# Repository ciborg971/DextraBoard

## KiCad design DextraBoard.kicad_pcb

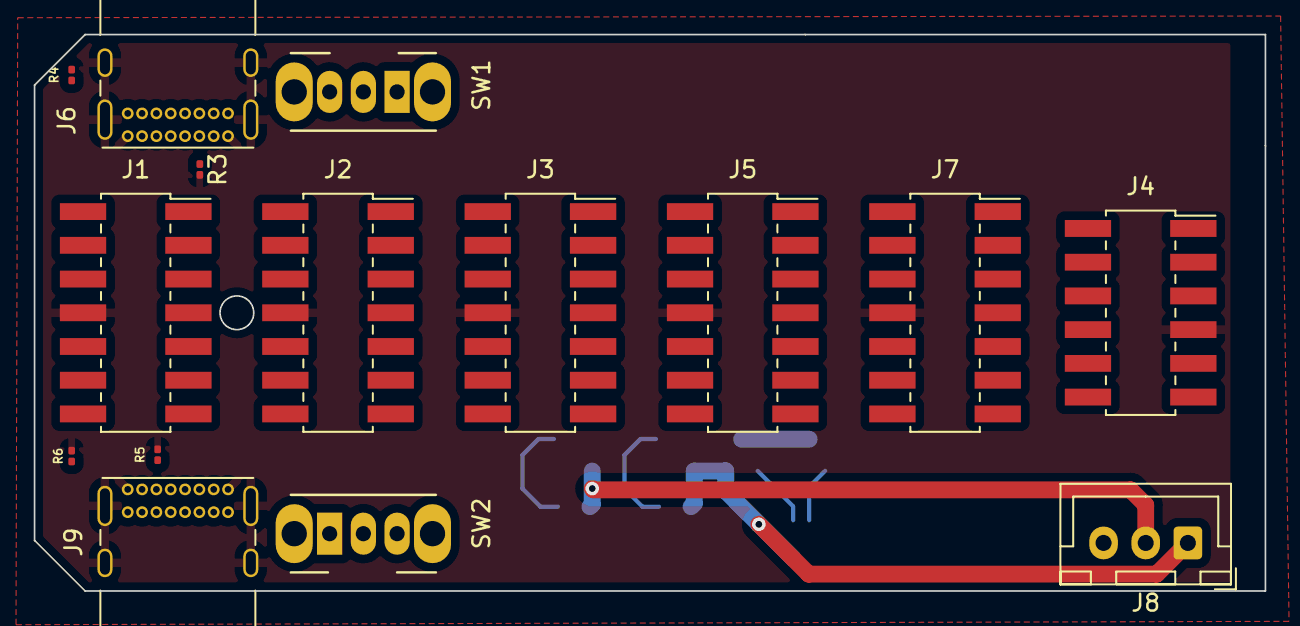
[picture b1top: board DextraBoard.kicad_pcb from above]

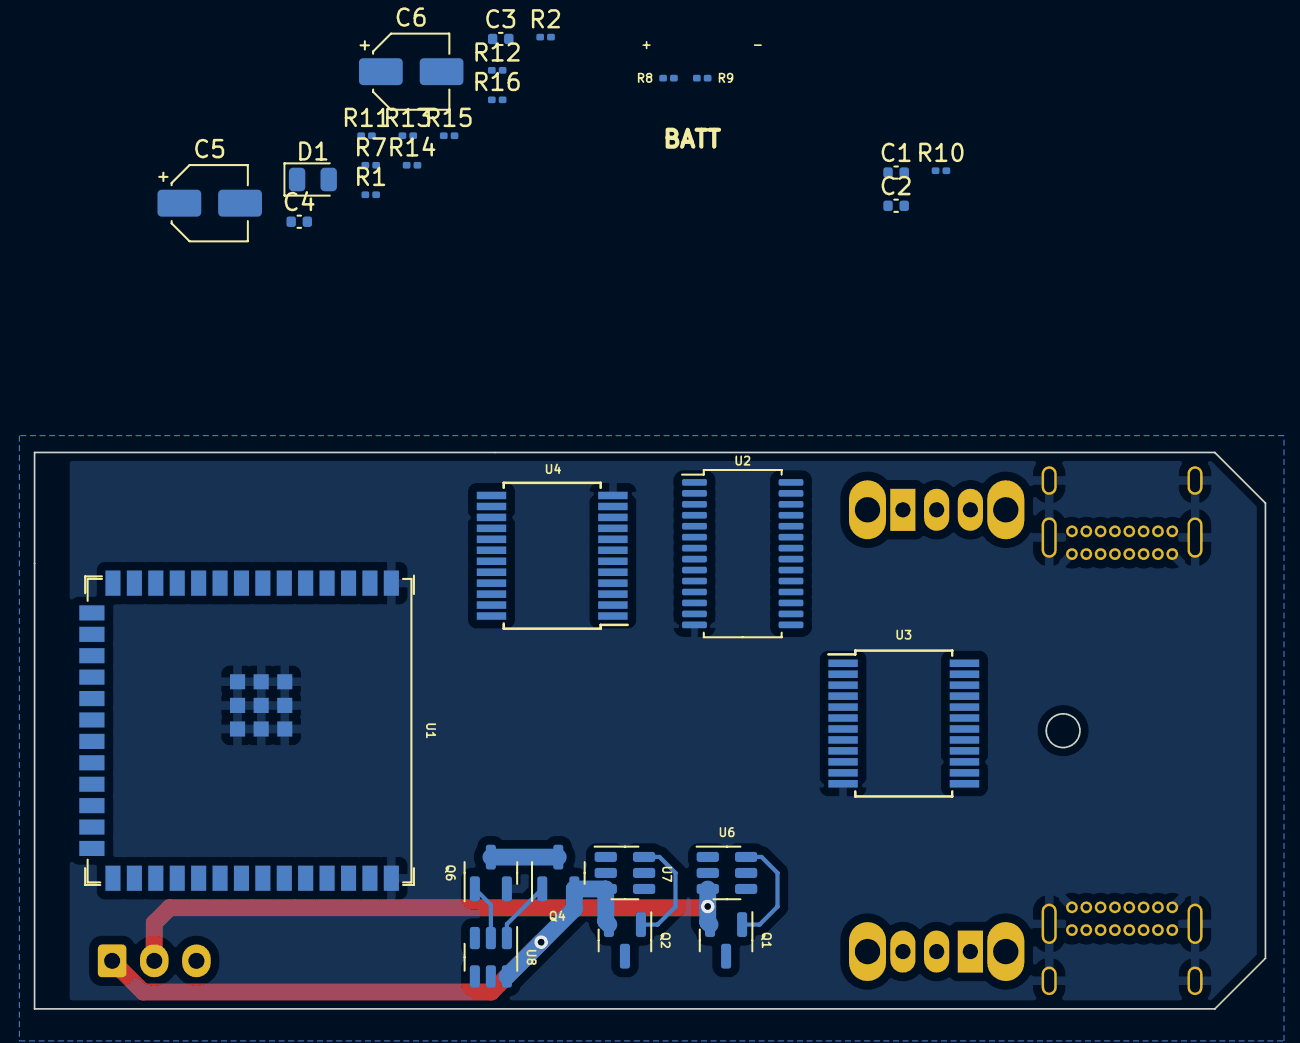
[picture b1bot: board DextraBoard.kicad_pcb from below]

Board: 4 copper layers, 73.0 x 33.0 mm, 45 parts (30 on the bottom side), 88 nets.

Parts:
C1, C2, C3, C4: 0.1uF; C_0402_1005Metric
C5, C6: 0.1uF; CP_Elec_4x3
D1: LED; LED_0805_2012Metric
J1, J2, J3, J5, J7: Conn_02x07_Counter_Clockwise; PinSocket_2x07_P2.00mm_Vertical_SMD
J4: Conn_02x06_Counter_Clockwise; PinSocket_2x06_P2.00mm_Vertical_SMD
J6, J9: USB_C_Receptacle_USB2.0; USB_C_Receptacle_GCT_USB4085
J8: Conn_01x03_Female; JST_XH_B3B-XH-A_1x03_P2.50mm_Vertical
Q1, Q2, Q4, Q6: HX2300A; SOT-23
R1, R2: 100R; R_0201_0603Metric
R3, R4, R5, R6: 5K1; R_0201_0603Metric
R7, R13: R; R_0201_0603Metric
R8: 2M; R_0201_0603Metric
R9: 1M; R_0201_0603Metric
R10: 10K; R_0201_0603Metric
R11, R12: 1K; R_0201_0603Metric
R14: 2K; R_0201_0603Metric
R15, R16: 330R; R_0201_0603Metric
SW1, SW2: SW_SPDT; SW_CuK_OS102011MA1QN1_SPDT_Angled
U1: ESP32-S3-WROOM-1; ESP32-S3-WROOM-1U
U2: PCA9685PW; TSSOP-28_4.4x9.7mm_P0.65mm
U3, U4: CD74HC4067SM; SSOP-24_5.3x8.2mm_P0.65mm
U6, U7: HY2213; SOT-23-6
U8: HY2120; SOT-23-6

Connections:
+3.3V: R13.2, U2.28 (VDD), U3.24 (VCC), U4.24 (VCC)
+3V3: J1.7, J2.7, J3.7, J4.4, J5.7, J7.7, R10.1, U1.2 (3V3)
+5V: J1.1, J2.1, J3.1, J4.1, J5.1, J7.1
+BATT: C3.1, J8.3, R1.1, R8.2, R9.2, R11.1, R15.2, SW1.3 (C), SW2.3 (C)
-BATT: C4.2, C5.2, C6.2, J8.1, Q2.2 (S), Q4.2 (S), U7.3 (VSS), U8.6 (VSS)
/ANA0: J4.10, U1.39 (GPIO1/TOUCH1/ADC1_CH0)
/ANA1: J4.9, U1.38 (GPIO2/TOUCH2/ADC1_CH1)
/ANA2: J4.8, U1.15 (GPIO3/TOUCH3/ADC1_CH2)
/ANA3: U1.4 (GPIO4/TOUCH4/ADC1_CH3), U3.1 (COM)
/ANA4: U1.5 (GPIO5/TOUCH5/ADC1_CH4), U4.1 (COM)
/HY_VDD: C5.1, R16.1, U8.5 (VDD)
/IO7: U1.7 (GPIO7/TOUCH7/ADC1_CH6), U3.10 (S0), U4.10 (S0)
/IO8: U1.12 (GPIO8/TOUCH8/ADC1_CH7/SUBSPICS1), U3.11 (S1), U4.11 (S1)
/IO9: U1.17 (GPIO9/TOUCH9/ADC1_CH8/FSPIHD/SUBSPIHD), U3.14 (S2), U4.14 (S2)
/IO10: U1.18 (GPIO10/TOUCH10/ADC1_CH9/FSPICS0/FSPIIO4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), U3.13 (S3), U4.13 (S3)
/IO13: J4.12, U1.21 (GPIO13/TOUCH13/ADC2_CH2/FSPIQ/FSPIIO7/S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)
/IO14: J4.6, U1.22 (GPIO14/TOUCH14/ADC2_CH3/FSPIWP/FSPIDQS/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)
/IO15: J4.11, U1.8 (GPIO15/U0RTS/ADC2_CH4/XTAL_32K_P)
/MID_BAT: C3.2, C4.1, J8.2, Q1.2 (S), R2.1, R12.1, R16.2, U6.3 (VSS)
/N76E003s (PWM + ADC + IO)/MUX_CH0: J1.14, U3.9 (I0)
/N76E003s (PWM + ADC + IO)/MUX_CH1: J1.13, U3.8 (I1)
/N76E003s (PWM + ADC + IO)/MUX_CH2: J1.12, U3.7 (I2)
/N76E003s (PWM + ADC + IO)/MUX_CH3: J1.11, U3.6 (I3)
/N76E003s (PWM + ADC + IO)/MUX_CH4: J1.10, U3.5 (I4)
/N76E003s (PWM + ADC + IO)/MUX_CH5: J1.9, U3.4 (I5)
/N76E003s (PWM + ADC + IO)/MUX_CH6: J2.14, U3.3 (I6)
/N76E003s (PWM + ADC + IO)/MUX_CH7: J2.13, U3.2 (I7)
/N76E003s (PWM + ADC + IO)/MUX_CH8: J2.12, U3.23 (I8)
/N76E003s (PWM + ADC + IO)/MUX_CH9: J2.11, U3.22 (I9)
/N76E003s (PWM + ADC + IO)/MUX_CH10: J2.10, U3.21 (I10)
/N76E003s (PWM + ADC + IO)/MUX_CH11: J2.9, U3.20 (I11)
/N76E003s (PWM + ADC + IO)/MUX_CH12: J3.14, U3.19 (I12)
/N76E003s (PWM + ADC + IO)/MUX_CH13: J3.13, U3.18 (I13)
/N76E003s (PWM + ADC + IO)/MUX_CH14: J3.12, U3.17 (I14)
/N76E003s (PWM + ADC + IO)/MUX_CH15: J3.11, U3.16 (I15)
/N76E003s (PWM + ADC + IO)/MUX_CH16: J3.10, U4.9 (I0)
/N76E003s (PWM + ADC + IO)/MUX_CH17: J3.9, U4.8 (I1)
/N76E003s (PWM + ADC + IO)/MUX_CH18: J5.14, U4.7 (I2)
/N76E003s (PWM + ADC + IO)/MUX_CH19: J5.13, U4.6 (I3)
/N76E003s (PWM + ADC + IO)/MUX_CH20: J5.12, U4.5 (I4)
/N76E003s (PWM + ADC + IO)/MUX_CH21: J5.11, U4.4 (I5)
/N76E003s (PWM + ADC + IO)/MUX_CH22: J5.10, U4.3 (I6)
/N76E003s (PWM + ADC + IO)/MUX_CH23: J5.9, U4.2 (I7)
/N76E003s (PWM + ADC + IO)/MUX_CH24: J7.14, U4.23 (I8)
/N76E003s (PWM + ADC + IO)/MUX_CH25: J7.13, U4.22 (I9)
/N76E003s (PWM + ADC + IO)/MUX_CH26: J7.12, U4.21 (I10)
/N76E003s (PWM + ADC + IO)/MUX_CH27: J7.11, U4.20 (I11)
/N76E003s (PWM + ADC + IO)/MUX_CH28: J7.10, U4.19 (I12)
/N76E003s (PWM + ADC + IO)/MUX_CH29: J7.9, U4.18 (I13)
/N76E003s (PWM + ADC + IO)/PWM4: J1.4, J5.4, U2.10 (LED4)
/N76E003s (PWM + ADC + IO)/PWM5: J1.5, J5.5, U2.11 (LED5)
/N76E003s (PWM + ADC + IO)/PWM6: J3.2, U2.12 (LED6)
/N76E003s (PWM + ADC + IO)/PWM7: J3.3, U2.13 (LED7)
/N76E003s (PWM + ADC + IO)/PWM8: J3.4, U2.15 (LED8)
/N76E003s (PWM + ADC + IO)/PWM9: J3.5, U2.16 (LED9)
/N76E003s (PWM + ADC + IO)/PWM10: J2.2, U2.17 (LED10)
/N76E003s (PWM + ADC + IO)/PWM11: J2.3, U2.18 (LED11)
/N76E003s (PWM + ADC + IO)/PWM12: J2.4, U2.19 (LED12)
/N76E003s (PWM + ADC + IO)/PWM13: J2.5, U2.20 (LED13)
/N76E003s (PWM + ADC + IO)/PWM14: J1.2, U2.21 (LED14)
/N76E003s (PWM + ADC + IO)/PWM15: J1.3, U2.22 (LED15)
/OC: Q6.1 (G), U8.2 (OC)
/OD: Q4.1 (G), U8.1 (OD)
/PWM0: J4.2, J7.2, U1.23 (GPIO21), U2.6 (LED0)
/PWM1: J4.3, J7.3, U1.26 (GPIO45), U2.7 (LED1)
/PWM2: J5.2, J7.5, U1.16 (GPIO46), U2.8 (LED2)
/PWM3: J5.3, J7.4, U1.25 (GPIO48/SPICLK_N/SUBSPICLK_N_DIFF), U2.9 (LED3)
/USB_DN: J6.A7 (D-), J6.B7 (D-), J9.A7 (D-), J9.B7 (D-), U1.13 (GPIO19/U1RTS/ADC2_CH8/CLK_OUT2/USB_D-)
/USB_DP: J6.A6 (D+), J6.B6 (D+), J9.A6 (D+), J9.B6 (D+), U1.14 (GPIO20/U1CTS/ADC2_CH9/CLK_OUT1/USB_D+)
/VIN: SW1.2 (B), SW2.2 (B)
/VSENSE: R8.1, U1.6 (GPIO6/TOUCH6/ADC1_CH5)
GND: C1.1, C2.1, J1.8, J2.8, J3.8, J4.7, J5.8, J6.A1 (GND), J6.A12 (GND), J6.B1 (GND), J6.B12 (GND), J6.S1 (SHIELD), J7.8, J9.A1 (GND), J9.A12 (GND), J9.B1 (GND), J9.B12 (GND), J9.S1 (SHIELD), Q6.2 (S), R3.2, R4.2, R5.2, R6.2, R7.2, R9.1, R14.1, U1.1 (GND), U1.40 (GND), U1.41 (GND), U2.14 (VSS), U3.12 (GND), U3.15 (~E), U4.12 (GND), U4.15 (~E)
unnamed: C1.2, C2.2, R10.2
unnamed: C6.1, R15.1, U8.4 (VC)
unnamed: D1.2 (A), R13.1
unnamed: J6.A5 (CC1), R3.1
unnamed: J6.B5 (CC2), R4.1
unnamed: J9.A5 (CC1), R5.1
unnamed: J9.B5 (CC2), R6.1
unnamed: Q1.1 (G), U6.6 (OUT)
unnamed: Q1.3 (D), R11.2
unnamed: Q2.1 (G), U7.6 (OUT)
unnamed: Q2.3 (D), R12.2
unnamed: Q4.3 (D), Q6.3 (D)
unnamed: R1.2, U6.2 (VDD)
unnamed: R2.2, U7.2 (VDD)
unnamed: R14.2, U8.3 (CS)
VBUS: J6.A4 (VBUS), J6.A9 (VBUS), J6.B4 (VBUS), J6.B9 (VBUS), J9.A4 (VBUS), J9.A9 (VBUS), J9.B4 (VBUS), J9.B9 (VBUS), SW1.1 (A), SW2.1 (A)

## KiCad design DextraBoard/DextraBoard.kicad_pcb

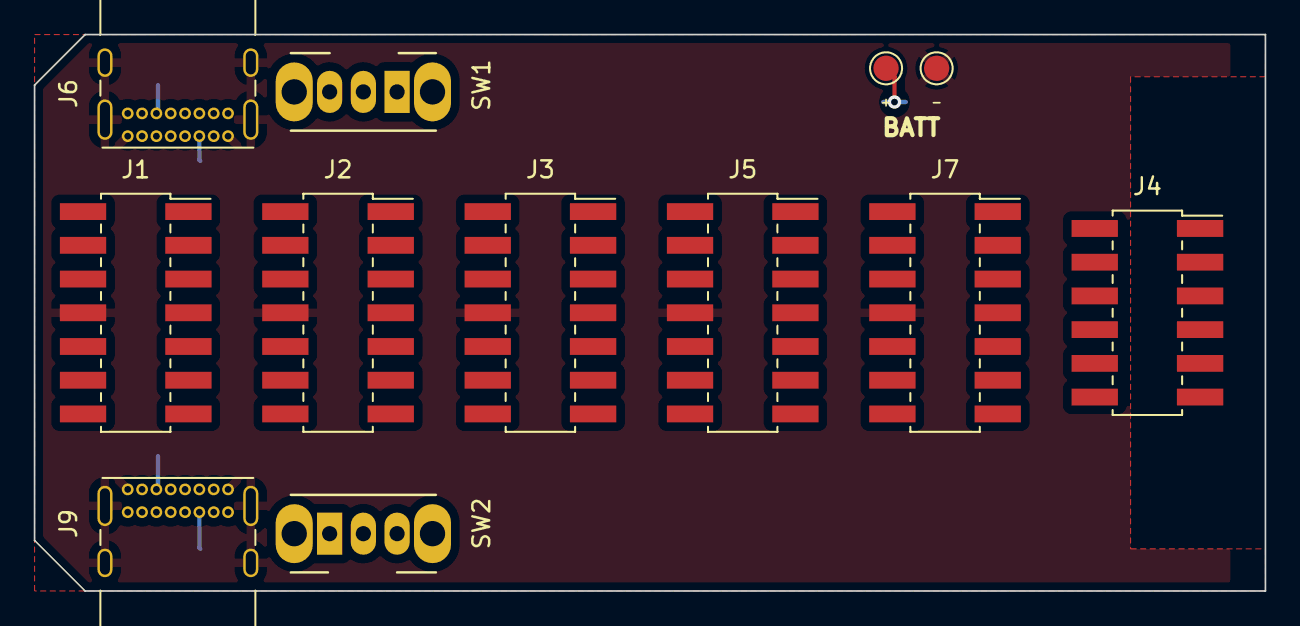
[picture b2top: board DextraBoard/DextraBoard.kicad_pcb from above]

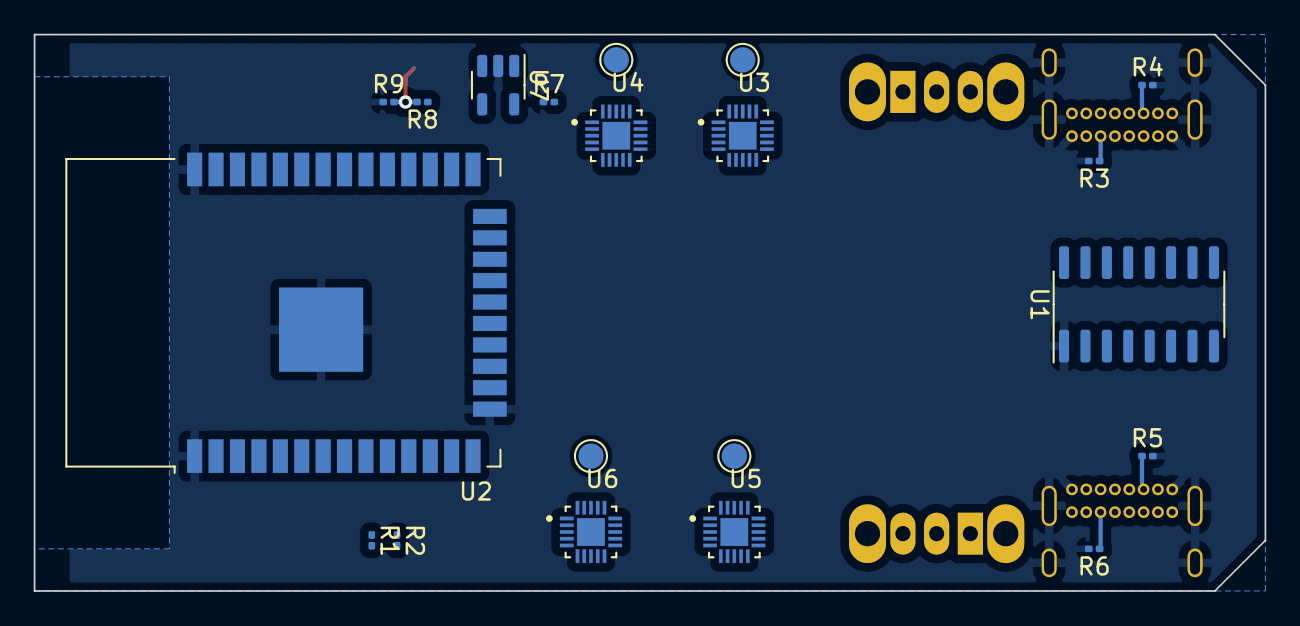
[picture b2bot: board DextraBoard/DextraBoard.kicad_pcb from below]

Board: 2 copper layers, 73.0 x 33.0 mm, 32 parts (20 on the bottom side), 83 nets.

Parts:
J1, J2, J3, J5, J7: Conn_02x07_Counter_Clockwise; PinSocket_2x07_P2.00mm_Vertical_SMD
J4: Conn_02x06_Counter_Clockwise; PinSocket_2x06_P2.00mm_Vertical_SMD
J6, J9: USB_C_Receptacle_USB2.0; USB_C_Receptacle_GCT_USB4085
R1, R2: 10K; R_0201_0603Metric
R3, R4, R5, R6: 5K1; R_0201_0603Metric
R7: R; R_0201_0603Metric
R8, R9: 1M; R_0201_0603Metric
SW1, SW2: SW_SPDT; SW_CuK_OS102011MA1QN1_SPDT_Angled
TP1, TP2, TP3, TP4, TP5, TP6: TestPoint; TestPoint_Pad_D1.5mm
U1: CH340C; SOIC-16_3.9x9.9mm_P1.27mm
U2: ESP32-WROOM-32D; ESP32-WROOM-32
U3, U4, U5, U6: N76E003AQ20; QFN40P300X300X80-21N
U7: MCP73811T-420I-OT; SOT-23-5

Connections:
+3V3: J1.7, J2.7, J3.7, J4.4, J5.7, J7.7, R1.1, R2.1, U2.2 (VDD), U3.5 (VDD), U4.5 (VDD), U5.5 (VDD), U6.5 (VDD)
+5V: J1.1, J2.1, J3.1, J4.1, J5.1, J7.1
+BATT: R8.2, R9.2, SW1.3 (C), SW2.3 (C), TP1.1, U7.3 (VBAT)
/ANA0: J7.10, U2.9 (IO33)
/ANA1: J7.9, U2.6 (IO34)
/ANA2: J4.10, U2.7 (IO35)
/ANA3: J4.9, U2.5 (SENSOR_VN)
/ANA4: J4.8, U2.4 (SENSOR_VP)
/I2C_SCL: R2.2, U2.36 (IO22), U3.11 (P1.3/SCL), U4.11 (P1.3/SCL), U5.11 (P1.3/SCL), U6.11 (P1.3/SCL)
/I2C_SDA: R1.2, U2.33 (IO21), U3.10 (P1.4/SDA/FB/PWM1), U4.10 (P1.4/SDA/FB/PWM1), U5.10 (P1.4/SDA/FB/PWM1), U6.10 (P1.4/SDA/FB/PWM1)
/N76E003s (PWM + ADC + IO)/ANA0_0: J1.14, U3.2 (P1.7/~INT1/AIN0)
/N76E003s (PWM + ADC + IO)/ANA0_1: J1.13, U3.17 (P3.0/~INT0/OSCIN/AIN1)
/N76E003s (PWM + ADC + IO)/ANA0_2: J1.12, U3.1 (P0.7/RXD/AIN2)
/N76E003s (PWM + ADC + IO)/ANA0_3: J1.11, U3.19 (P0.6/TXD/AIN3)
/N76E003s (PWM + ADC + IO)/ANA0_4: J1.10, U3.20 (P0.5/PWM2/IC6/T0/AIN4)
/N76E003s (PWM + ADC + IO)/ANA0_5: J1.9, U3.16 (P0.4/AIN5/STADC/PWM3/IC3)
/N76E003s (PWM + ADC + IO)/ANA0_6: J2.14, U3.15 (P0.3/PWM5/IC5/AIN6)
/N76E003s (PWM + ADC + IO)/ANA1_0: J2.13, U4.2 (P1.7/~INT1/AIN0)
/N76E003s (PWM + ADC + IO)/ANA1_1: J2.12, U4.17 (P3.0/~INT0/OSCIN/AIN1)
/N76E003s (PWM + ADC + IO)/ANA1_2: J2.11, U4.1 (P0.7/RXD/AIN2)
/N76E003s (PWM + ADC + IO)/ANA1_3: J2.10, U4.19 (P0.6/TXD/AIN3)
/N76E003s (PWM + ADC + IO)/ANA1_4: J2.9, U4.20 (P0.5/PWM2/IC6/T0/AIN4)
/N76E003s (PWM + ADC + IO)/ANA1_5: J3.14, U4.16 (P0.4/AIN5/STADC/PWM3/IC3)
/N76E003s (PWM + ADC + IO)/ANA1_6: J3.13, U4.15 (P0.3/PWM5/IC5/AIN6)
/N76E003s (PWM + ADC + IO)/ANA2_0: J3.12, U5.2 (P1.7/~INT1/AIN0)
/N76E003s (PWM + ADC + IO)/ANA2_1: J3.11, U5.17 (P3.0/~INT0/OSCIN/AIN1)
/N76E003s (PWM + ADC + IO)/ANA2_2: J3.10, U5.1 (P0.7/RXD/AIN2)
/N76E003s (PWM + ADC + IO)/ANA2_3: J3.9, U5.19 (P0.6/TXD/AIN3)
/N76E003s (PWM + ADC + IO)/ANA2_4: J5.14, U5.20 (P0.5/PWM2/IC6/T0/AIN4)
/N76E003s (PWM + ADC + IO)/ANA2_5: J5.13, U5.16 (P0.4/AIN5/STADC/PWM3/IC3)
/N76E003s (PWM + ADC + IO)/ANA2_6: J5.12, U5.15 (P0.3/PWM5/IC5/AIN6)
/N76E003s (PWM + ADC + IO)/ANA3_0: J5.11, U6.2 (P1.7/~INT1/AIN0)
/N76E003s (PWM + ADC + IO)/ANA3_1: J5.10, U6.17 (P3.0/~INT0/OSCIN/AIN1)
/N76E003s (PWM + ADC + IO)/ANA3_2: J5.9, U6.1 (P0.7/RXD/AIN2)
/N76E003s (PWM + ADC + IO)/ANA3_3: J7.14, U6.19 (P0.6/TXD/AIN3)
/N76E003s (PWM + ADC + IO)/ANA3_4: J7.13, U6.20 (P0.5/PWM2/IC6/T0/AIN4)
/N76E003s (PWM + ADC + IO)/ANA3_5: J7.12, U6.16 (P0.4/AIN5/STADC/PWM3/IC3)
/N76E003s (PWM + ADC + IO)/ANA3_6: J7.11, U6.15 (P0.3/PWM5/IC5/AIN6)
/N76E003s (PWM + ADC + IO)/PWM0_0: J1.2, U3.9 (P1.2/PWM0/IC0)
/N76E003s (PWM + ADC + IO)/PWM0_1: J1.3, U3.8 (P1.1/PWM1/IC1/AIN7/CLO)
/N76E003s (PWM + ADC + IO)/PWM0_2: J1.4, U3.7 (P1.0/PWM2/IC2/SPCLK)
/N76E003s (PWM + ADC + IO)/PWM0_3: J1.5, U3.12 (P0.0/PWM3/IC3/MOSI/T1)
/N76E003s (PWM + ADC + IO)/PWM0_4: J2.2, U3.13 (P0.1/PWM4/IC4/MISO)
/N76E003s (PWM + ADC + IO)/PWM0_5: J2.3, U3.6 (P1.5/PWM5/IC7/~SS)
/N76E003s (PWM + ADC + IO)/PWM1_0: J2.4, U4.9 (P1.2/PWM0/IC0)
/N76E003s (PWM + ADC + IO)/PWM1_1: J2.5, U4.8 (P1.1/PWM1/IC1/AIN7/CLO)
/N76E003s (PWM + ADC + IO)/PWM1_2: J3.2, U4.7 (P1.0/PWM2/IC2/SPCLK)
/N76E003s (PWM + ADC + IO)/PWM1_3: J3.3, U4.12 (P0.0/PWM3/IC3/MOSI/T1)
/N76E003s (PWM + ADC + IO)/PWM1_4: J3.4, U4.13 (P0.1/PWM4/IC4/MISO)
/N76E003s (PWM + ADC + IO)/PWM1_5: J3.5, U4.6 (P1.5/PWM5/IC7/~SS)
/N76E003s (PWM + ADC + IO)/PWM2_0: J5.2, U5.9 (P1.2/PWM0/IC0)
/N76E003s (PWM + ADC + IO)/PWM2_1: J5.3, U5.8 (P1.1/PWM1/IC1/AIN7/CLO)
/N76E003s (PWM + ADC + IO)/PWM2_2: J5.4, U5.7 (P1.0/PWM2/IC2/SPCLK)
/N76E003s (PWM + ADC + IO)/PWM2_3: J5.5, U5.12 (P0.0/PWM3/IC3/MOSI/T1)
/N76E003s (PWM + ADC + IO)/PWM2_4: J7.2, U5.13 (P0.1/PWM4/IC4/MISO)
/N76E003s (PWM + ADC + IO)/PWM2_5: J7.3, U5.6 (P1.5/PWM5/IC7/~SS)
/N76E003s (PWM + ADC + IO)/PWM3_0: J7.4, U6.9 (P1.2/PWM0/IC0)
/N76E003s (PWM + ADC + IO)/PWM3_1: J7.5, U6.8 (P1.1/PWM1/IC1/AIN7/CLO)
/N76E003s (PWM + ADC + IO)/RXD0: J1.6, U3.14 (P0.2/ICPCK/OCDCK/RXD_1)
/N76E003s (PWM + ADC + IO)/RXD1: J3.6, U4.14 (P0.2/ICPCK/OCDCK/RXD_1)
/N76E003s (PWM + ADC + IO)/RXD2: J7.6, U5.14 (P0.2/ICPCK/OCDCK/RXD_1)
/N76E003s (PWM + ADC + IO)/RXD3: J4.6, U6.14 (P0.2/ICPCK/OCDCK/RXD_1)
/N76E003s (PWM + ADC + IO)/TXD0: J2.6, U3.4 (P1.6/ICPDA/OCDDA/TXD_1)
/N76E003s (PWM + ADC + IO)/TXD1: J5.6, U4.4 (P1.6/ICPDA/OCDDA/TXD_1)
/N76E003s (PWM + ADC + IO)/TXD2: J4.5, U5.4 (P1.6/ICPDA/OCDDA/TXD_1)
/N76E003s (PWM + ADC + IO)/TXD3: J4.11, J4.12, U6.4 (P1.6/ICPDA/OCDDA/TXD_1)
/PWM0: J4.2, U2.11 (IO26)
/PWM1: J4.3, U2.12 (IO27)
/USB_DN: J6.A7 (D-), J6.B7 (D-), J9.A7 (D-), J9.B7 (D-), U1.6 (UD-)
/USB_DP: J6.A6 (D+), J6.B6 (D+), J9.A6 (D+), J9.B6 (D+), U1.5 (UD+)
/VIN: SW1.2 (B), SW2.2 (B)
/VSENSE: R8.1, U2.8 (IO32)
GND: J1.8, J2.8, J3.8, J4.7, J5.8, J6.A1 (GND), J6.A12 (GND), J6.B1 (GND), J6.B12 (GND), J6.S1 (SHIELD), J7.8, J9.A1 (GND), J9.A12 (GND), J9.B1 (GND), J9.B12 (GND), J9.S1 (SHIELD), R3.2, R4.2, R5.2, R6.2, R7.1, R9.1, TP2.1, U1.1 (GND), U2.1 (GND), U2.15 (GND), U2.38 (GND), U2.39 (GND), U3.3 (GND), U3.21 (EXP), U4.3 (GND), U4.21 (EXP), U5.3 (GND), U5.21 (EXP), U6.3 (GND), U6.21 (EXP), U7.2 (VSS)
unnamed: J6.A5 (CC1), R3.1
unnamed: J6.B5 (CC2), R4.1
unnamed: J9.A5 (CC1), R5.1
unnamed: J9.B5 (CC2), R6.1
unnamed: R7.2, U7.5 (PROG)
unnamed: TP3.1, U3.18 (P2.0/~RST)
unnamed: TP4.1, U4.18 (P2.0/~RST)
unnamed: TP5.1, U5.18 (P2.0/~RST)
unnamed: TP6.1, U6.18 (P2.0/~RST)
VBUS: J6.A4 (VBUS), J6.A9 (VBUS), J6.B4 (VBUS), J6.B9 (VBUS), J9.A4 (VBUS), J9.A9 (VBUS), J9.B4 (VBUS), J9.B9 (VBUS), SW1.1 (A), SW2.1 (A), U7.4 (VDD)

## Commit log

2022-08-24 component placement
2022-08-24 replaced esp32wroom by esp32 pico d4 and moved all component on one side
2022-12-01 redesigned everything x)
    new BMS design, switched to ESP32-S3 with external antenna, implement USB-C PD, add analog mux, add PWM controller, add USB to serial
